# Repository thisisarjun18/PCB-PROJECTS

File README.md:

# PCB-PROJECTS
PCB design projects created in KiCad, including schematic capture, PCB layout, routing, and hardware prototyping.

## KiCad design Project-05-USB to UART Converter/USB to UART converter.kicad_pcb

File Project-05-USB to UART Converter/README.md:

Overview

This project is a USB Type-C to UART Converter designed using the CP2102N USB-to-UART Bridge Controller.
It enables communication between a computer and microcontrollers, development boards, or embedded systems through a standard UART interface.
The board uses a USB Type-C connector for power and data transfer and exposes UART signals through external header pins.

Features
USB Type-C Interface
CP2102N USB-to-UART Bridge
UART Communication (TX/RX)
Reset Signal Access
Compact and Easy-to-Use Design
Plug-and-Play USB Connectivity
Suitable for Embedded Development and Debugging
Components Used
CP2102N USB-to-UART Bridge IC
USB Type-C Connector
Status LEDs
Decoupling Capacitors
Pull-up/Pull-down Resistors
UART Header Connector
PCB Designed in KiCad
Pin Configuration
Pin	Description
VBUS	+5V USB Supply
GND	Ground
TX	UART Transmit
RX	UART Receive
RST	Reset Signal
Working Principle
The USB Type-C connector receives power and USB data from the host computer.
The CP2102N enumerates as a virtual COM port on the operating system.
USB data is converted into UART serial data.
The TX and RX pins provide serial communication with external microcontrollers or embedded devices.
Status LEDs indicate power and communication activity.
Applications
Microcontroller Programming
Serial Debugging
Embedded System Development
Firmware Uploading
IoT Prototyping
UART Communication Testing

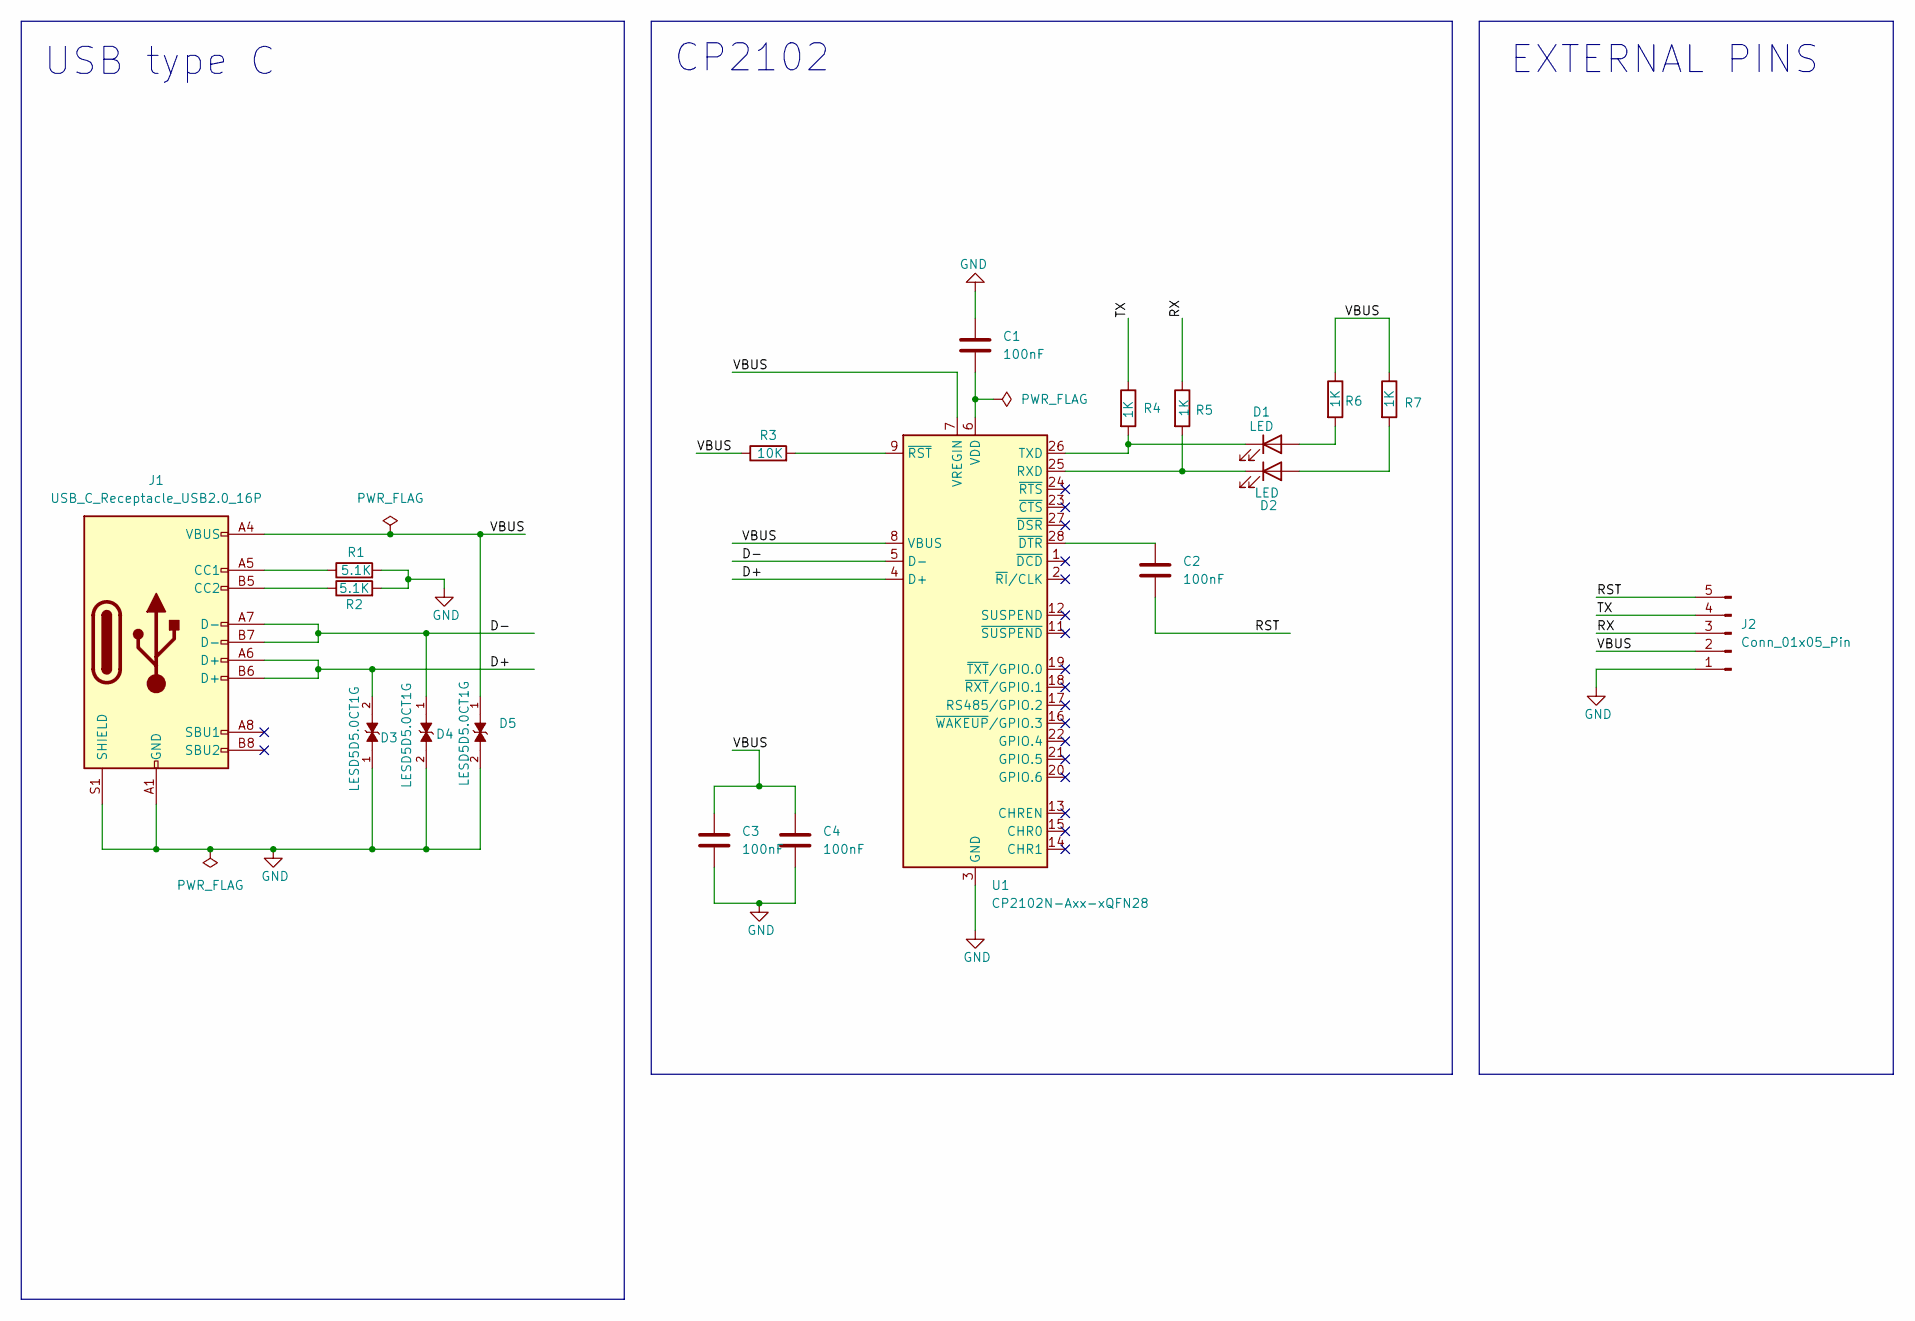
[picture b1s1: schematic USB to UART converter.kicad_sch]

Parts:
C1, C2, C3, C4: 100nF; C_0201_0603Metric
D1, D2: LED; LED_0201_0603Metric
D3, D4, D5: LESD5D5.0CT1G; TVS_LESD5D5.0CT1G; PARTREV O
J1: USB_C_Receptacle_USB2.0_16P; USB_C_Receptacle_HRO_TYPE-C-31-M-12
J2: Conn_01x05_Pin; PinHeader_1x05_P2.54mm_Horizontal
R1, R2: 5.1K; R_0201_0603Metric
R3: 10K; R_0201_0603Metric
R4, R5, R6, R7: 1K; R_0201_0603Metric
U1: CP2102N-Axx-xQFN28; QFN-28-1EP_5x5mm_P0.5mm_EP3.35x3.35mm

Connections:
/D+: D3.2, J1.A6 (D+), J1.B6 (D+), U1.4 (D+)
/D-: D4.1, J1.A7 (D-), J1.B7 (D-), U1.5 (D-)
/RST: C2.1, J2.5
/RX: J2.3, R5.1
/TX: J2.4, R4.1
/VBUS: C3.1, C4.1, D5.1, J1.A4 (VBUS), J1.A9 (VBUS), J1.B4 (VBUS), J1.B9 (VBUS), J2.2, R3.1, R6.1, R7.1, U1.7 (VREGIN), U1.8 (VBUS)
GND: C1.1, C3.2, C4.2, D3.1, D4.2, D5.2, J1.A1 (GND), J1.A12 (GND), J1.B1 (GND), J1.B12 (GND), J1.S1 (SHIELD), J2.1, R1.2, R2.2, U1.3 (GND), U1.29 (GND)
unnamed: D1.2 (A), R6.2
unnamed: D1.1 (K), R4.2, U1.26 (TXD)
unnamed: D2.2 (A), R7.2
unnamed: D2.1 (K), R5.2, U1.25 (RXD)
unnamed: J1.A5 (CC1), R1.1
unnamed: J1.B5 (CC2), R2.1
unnamed: C1.2, U1.6 (VDD)
unnamed: C2.2, U1.28 (~DTR)
unnamed: R3.2, U1.9 (~RST)

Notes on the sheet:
CP2102
USB type C
EXTERNAL PINS

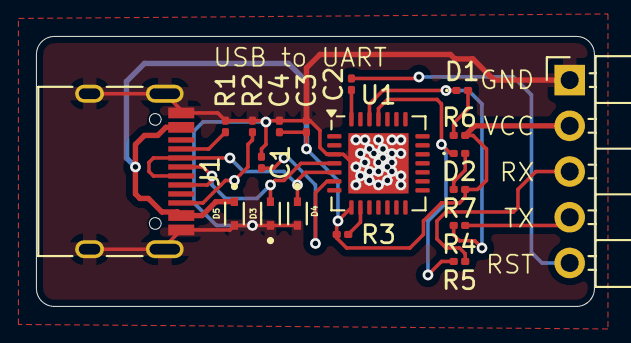
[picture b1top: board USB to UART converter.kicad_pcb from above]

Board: 2 copper layers, 31.0 x 15.0 mm, 19 parts (0 on the bottom side), 16 nets.

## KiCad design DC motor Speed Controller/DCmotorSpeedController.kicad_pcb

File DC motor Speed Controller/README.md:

Overview

This project implements a PWM-based DC Motor Speed Controller using the NE555 Timer IC and a TIP122 Darlington Transistor.
The speed of the motor is controlled by adjusting the duty cycle of the PWM signal through a potentiometer, 
allowing efficient motor speed regulation without significant power loss.

Circuit Description

The NE555 timer is configured in astable mode to generate a PWM signal.
A potentiometer and two diodes are used to independently control the charging and discharging paths of the timing capacitor,
enabling duty-cycle adjustment while maintaining a nearly constant frequency.

The generated PWM signal drives a TIP122 transistor, which acts as a switching element for the DC motor. 
A flyback diode protects the transistor from back-EMF generated by the motor.

Components Used
NE555 Timer IC
TIP122 Darlington Transistor
100kΩ Potentiometer
1kΩ Resistors (R1, R2)
2.2kΩ Resistor (R3)
1N4007 Diodes (D1, D2, D3)
LED Indicator
100nF Capacitors (C1, C2)
1000µF Capacitor (C3)
DC Motor
DC Power Supply
Features
PWM-based speed control
Smooth motor operation
Low component count
Back-EMF protection
Easy to build and understand
Suitable for learning PWM motor control concepts
Working Principle
The NE555 generates a PWM waveform.
The potentiometer adjusts the duty cycle.
The PWM output drives the TIP122 transistor.
The transistor switches power to the motor.
Higher duty cycle → Higher average voltage → Higher motor speed.
Lower duty cycle → Lower average voltage → Lower motor speed.
Applications
Robotics
DIY Electronics Projects
Fan Speed Controllers
Small Automation Systems
Educational Embedded Projects

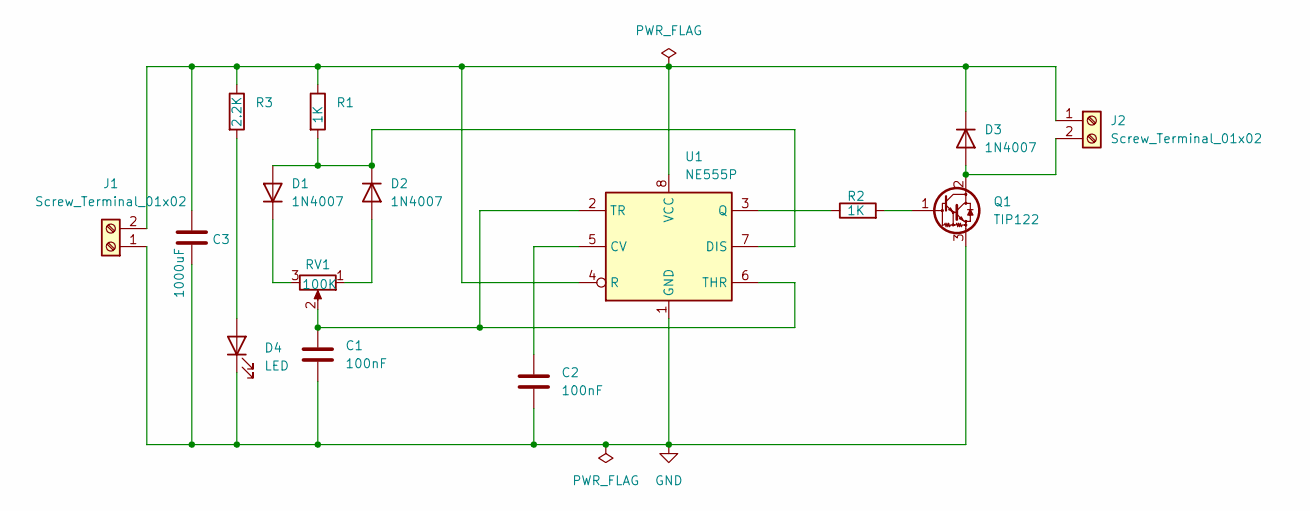
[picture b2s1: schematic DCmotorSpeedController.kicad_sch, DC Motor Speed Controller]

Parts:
C1, C2: 100nF; C_Disc_D4.7mm_W2.5mm_P5.00mm
C3: 1000uF; CP_Radial_D10.0mm_P5.00mm
D1, D2, D3: 1N4007; D_DO-41_SOD81_P10.16mm_Horizontal
D4: LED; LED_D5.0mm
J1, J2: Screw_Terminal_01x02; TerminalBlock_bornier-2_P5.08mm
Q1: TIP122; TO-220-3_Vertical
R1, R2: 1K; R_Axial_DIN0204_L3.6mm_D1.6mm_P7.62mm_Horizontal
R3: 2.2K; R_Axial_DIN0204_L3.6mm_D1.6mm_P7.62mm_Horizontal
RV1: 100K; Potentiometer_Alps_RK163_Single_Horizontal
U1: NE555P; DIP-8_W7.62mm

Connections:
GND: C1.2, C2.2, C3.2, D4.1 (K), J1.1, Q1.3 (E), U1.1 (GND)
unnamed: D1.2 (A), D2.1 (K), R1.2, U1.7 (DIS)
unnamed: D1.1 (K), RV1.3
unnamed: D2.2 (A), RV1.1
unnamed: D3.2 (A), J2.2, Q1.2 (C)
unnamed: C3.1, D3.1 (K), J1.2, J2.1, R1.1, R3.1, U1.4 (R), U1.8 (VCC)
unnamed: D4.2 (A), R3.2
unnamed: Q1.1 (B), R2.2
unnamed: C2.1, U1.5 (CV)
unnamed: R2.1, U1.3 (Q)
unnamed: C1.1, RV1.2, U1.2 (TR), U1.6 (THR)

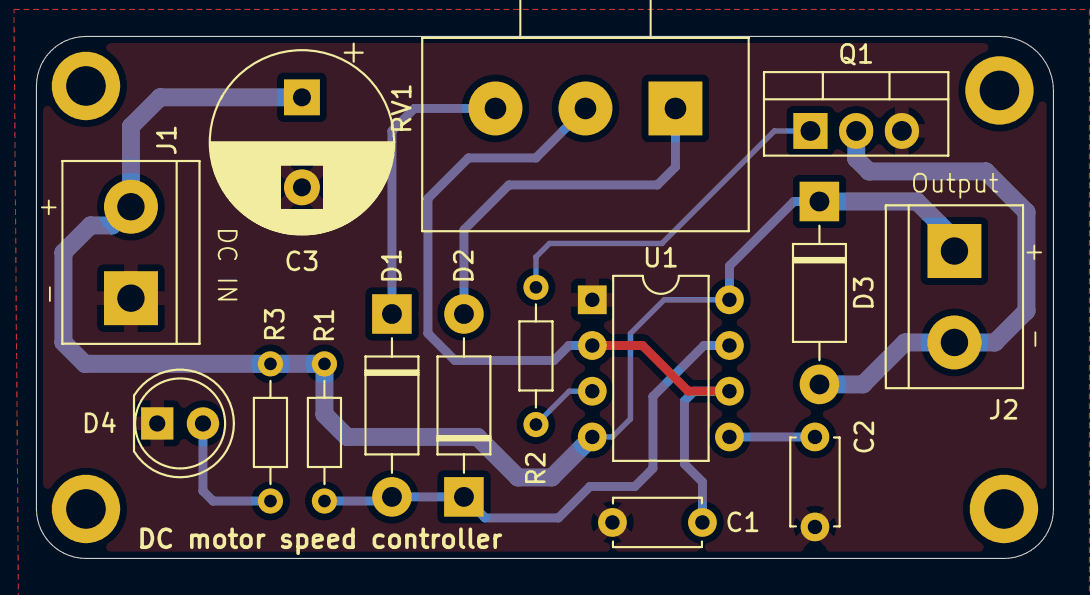
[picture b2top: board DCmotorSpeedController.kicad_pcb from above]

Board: 2 copper layers, 56.5 x 29.0 mm, 15 parts (0 on the bottom side), 11 nets.

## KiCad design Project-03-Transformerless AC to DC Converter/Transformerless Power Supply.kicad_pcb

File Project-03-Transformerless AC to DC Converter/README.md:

Transformerless AC to DC Converter PCB Design

Overview

This project is a PCB design of a Transformerless AC to DC Converter created using KiCad. The circuit converts AC input into regulated DC output using a capacitive dropper, bridge rectifier, filter capacitors, and a voltage regulator.

The design demonstrates fundamental concepts of power electronics, PCB layout design, component placement, routing, ground plane implementation, and Design Rule Checking (DRC).

Features

* AC to DC conversion without a transformer
* Bridge rectifier using four diodes
* Capacitive dropper technique
* Voltage regulation
* Ground plane implementation on the PCB
* Designed using KiCad 10
* DRC verified with no electrical errors

## Components Used

* Terminal Blocks
* Capacitive Dropper Capacitor
* Resistors
* Bridge Rectifier Diodes
* Electrolytic Capacitors
* Ceramic Capacitor
* Voltage Regulator
* LED Indicator

PCB Design Highlights

* Single PCB design with optimized component placement
* Ground plane implemented using copper pour
* Through-hole components for easy assembly
* Electrical Rule Check (ERC) and Design Rule Check (DRC) completed

Learning Outcomes

This project helped in understanding:

* AC to DC conversion principles
* Bridge rectifier operation
* Capacitor filtering
* Voltage regulation
* PCB routing techniques
* Ground plane implementation
* KiCad schematic and PCB workflow

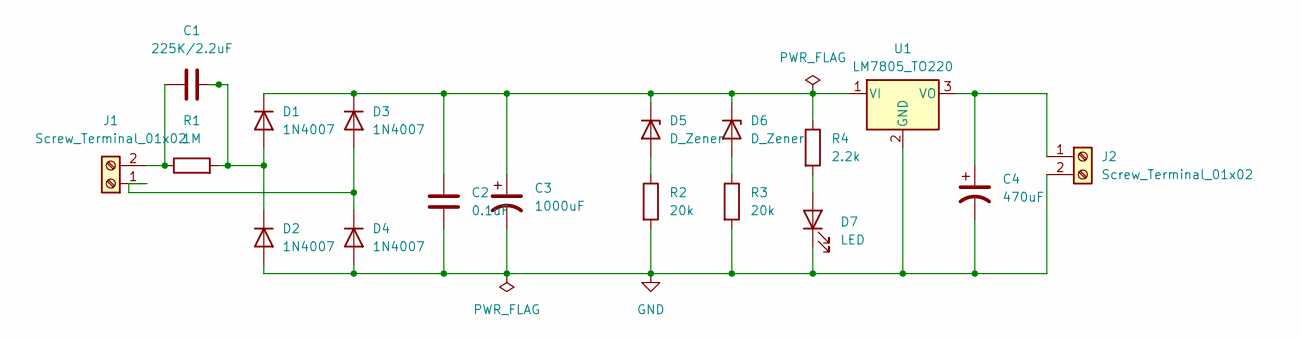
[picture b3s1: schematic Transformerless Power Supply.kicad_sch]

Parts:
C1: 225K/2.2uF; C_Rect_L10.0mm_W3.0mm_P7.50mm_FKS3_FKP3
C2: 0.1uF; C_Disc_D10.0mm_W2.5mm_P5.00mm
C3: 1000uF; CP_Radial_D10.0mm_P2.50mm
C4: 470uF; CP_Radial_D10.0mm_P3.80mm
D1, D2, D3, D4: 1N4007; D_DO-41_SOD81_P10.16mm_Horizontal
D5, D6: D_Zener; D_DO-15_P12.70mm_Horizontal
D7: LED; LED_D3.0mm
J1, J2: Screw_Terminal_01x02; TerminalBlock_MaiXu_MX126-5.0-02P_1x02_P5.00mm
R1: 1M; R_Axial_DIN0204_L3.6mm_D1.6mm_P5.08mm_Horizontal
R2, R3: 20k; R_Axial_DIN0204_L3.6mm_D1.6mm_P5.08mm_Horizontal
R4: 2.2k; R_Axial_DIN0204_L3.6mm_D1.6mm_P5.08mm_Horizontal
U1: LM7805_TO220; TO-220-3_Vertical

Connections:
GND: C2.2, C3.2, C4.2, D2.2 (A), D4.2 (A), D7.1 (K), J2.2, R2.2, R3.2, U1.2 (GND)
unnamed: C1.2, D1.2 (A), D2.1 (K), R1.2
unnamed: C2.1, C3.1, D1.1 (K), D3.1 (K), D5.1 (K), D6.1 (K), R4.1, U1.1 (VI)
unnamed: D3.2 (A), D4.1 (K), J1.1
unnamed: D5.2 (A), R2.1
unnamed: D6.2 (A), R3.1
unnamed: D7.2 (A), R4.2
unnamed: C1.1, J1.2, R1.1
unnamed: C4.1, J2.1, U1.3 (VO)

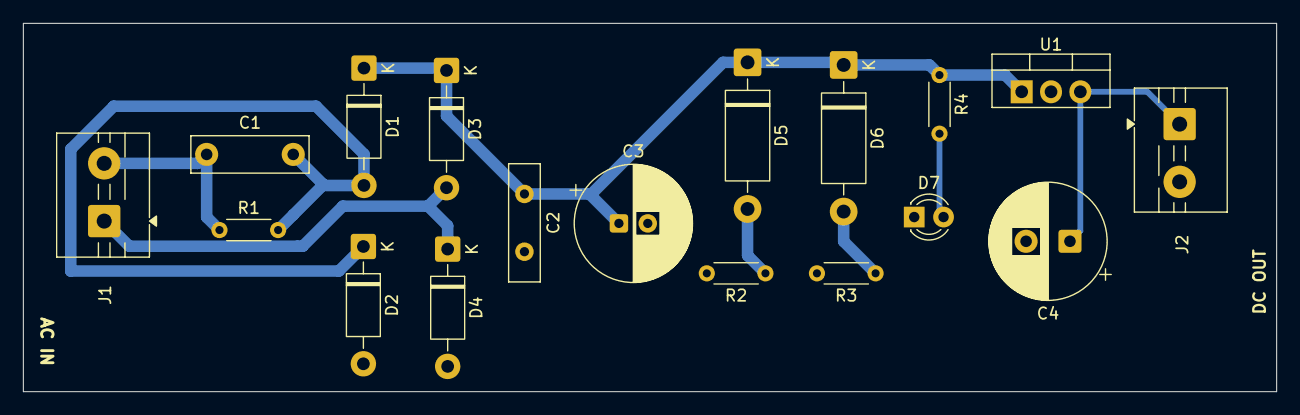
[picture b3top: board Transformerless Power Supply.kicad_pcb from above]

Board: 2 copper layers, 108.6 x 31.9 mm, 18 parts (0 on the bottom side), 9 nets.

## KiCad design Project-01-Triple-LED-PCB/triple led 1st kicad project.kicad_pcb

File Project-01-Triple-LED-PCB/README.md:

# Project 01 - Triple LED PCB

A simple 3-channel LED indicator PCB designed in KiCad.

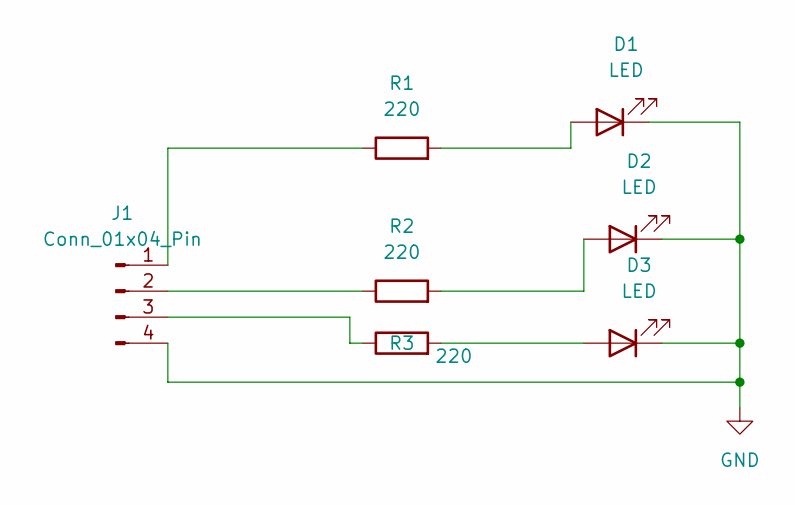
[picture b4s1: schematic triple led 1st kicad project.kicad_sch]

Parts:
D1, D2, D3: LED; LED_D5.0mm
J1: Conn_01x04_Pin; PinHeader_1x04_P1.00mm_Vertical
R1, R2, R3: 220; R_Axial_DIN0204_L3.6mm_D1.6mm_P5.08mm_Horizontal

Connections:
GND: D1.1 (K), D2.1 (K), D3.1 (K), J1.4
unnamed: D1.2 (A), R1.2
unnamed: D2.2 (A), R2.2
unnamed: D3.2 (A), R3.2
unnamed: J1.1, R1.1
unnamed: J1.2, R2.1
unnamed: J1.3, R3.1

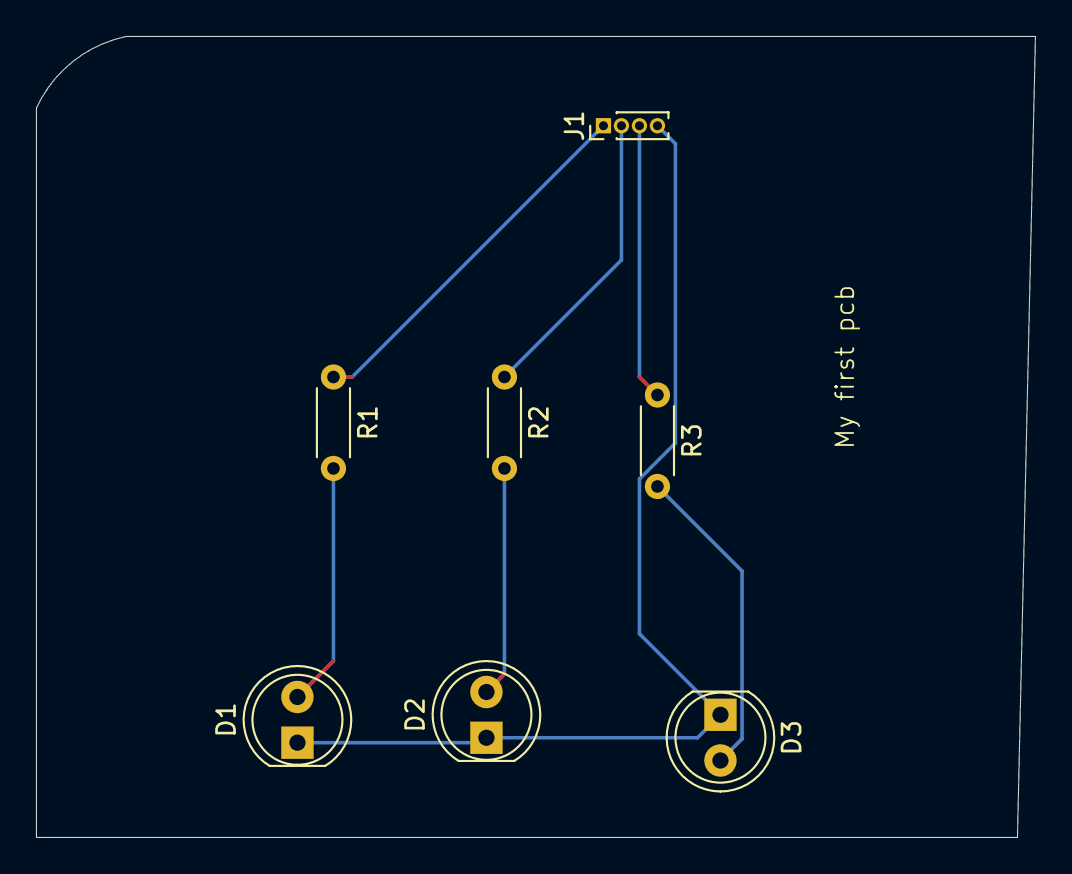
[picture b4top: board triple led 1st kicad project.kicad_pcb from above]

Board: 2 copper layers, 55.5 x 44.5 mm, 7 parts (0 on the bottom side), 7 nets.

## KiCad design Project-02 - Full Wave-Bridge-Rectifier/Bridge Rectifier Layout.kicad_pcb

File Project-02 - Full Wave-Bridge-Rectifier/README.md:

# Project 02 - Full Wave Bridge Rectifier

## Overview
A full-wave bridge rectifier PCB designed in KiCad to convert AC voltage into DC voltage using four 1N4007 diodes, a filter capacitor, and an LED power indicator.

## Components Used
- 4 × 1N4007 Diodes
- 1 × 1000µF Capacitor
- 1 × LED
- 1 × 2.2kΩ Resistor
- 2 × Screw Terminal Connectors

## Features
- Full-wave AC to DC conversion
- Capacitor filtering for smoother DC output
- LED power indication
- Through-hole components

## Tools Used
- KiCad 10

## Learning Outcomes
- Bridge rectifier operation
- AC to DC conversion
- Capacitor filtering
- Schematic design
- PCB layout and routing

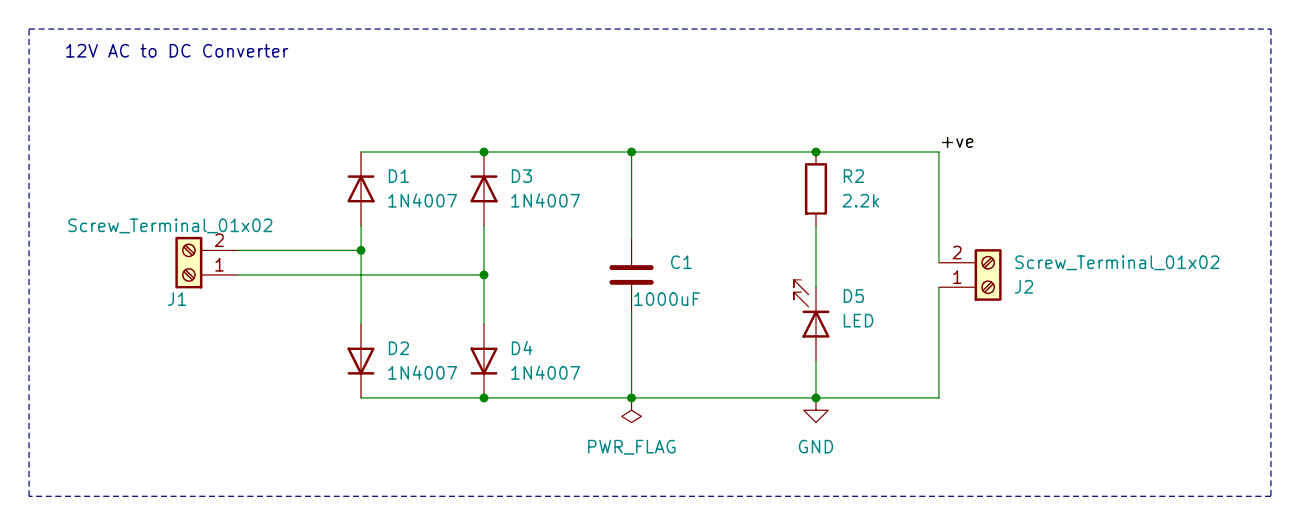
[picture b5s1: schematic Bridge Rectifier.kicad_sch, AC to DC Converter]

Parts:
C1: 1000uF; CP_Radial_D10.0mm_P3.50mm
D1, D2, D3, D4: 1N4007; D_DO-41_SOD81_P10.16mm_Horizontal
D5: LED; LED_D10.0mm
J1, J2: Screw_Terminal_01x02
R2: 2.2k; R_Axial_DIN0207_L6.3mm_D2.5mm_P10.16mm_Horizontal

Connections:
/+ve: C1.1, D1.1 (K), D3.1 (K), J2.2, R2.1
GND: C1.2, D2.1 (K), D4.1 (K), D5.2 (A), J2.1
unnamed: D1.2 (A), D2.2 (A), J1.2
unnamed: D3.2 (A), D4.2 (A), J1.1
unnamed: D5.1 (K), R2.2

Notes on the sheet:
12V AC to DC Converter

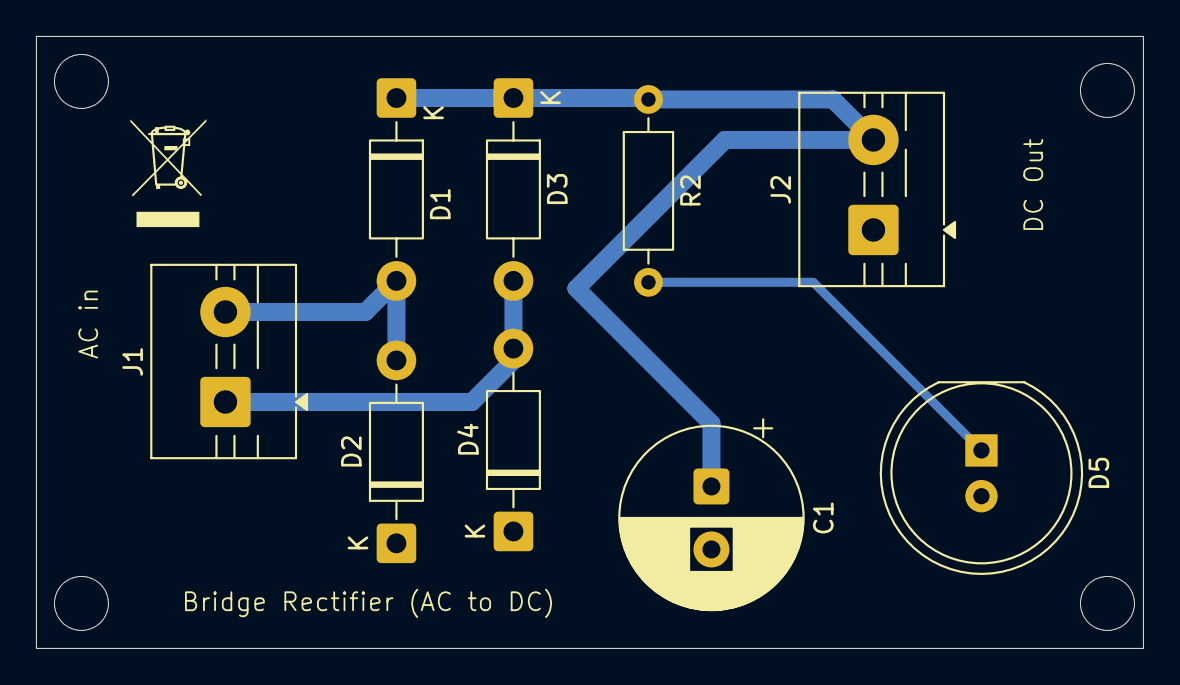
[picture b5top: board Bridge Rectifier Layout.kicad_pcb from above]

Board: 2 copper layers, 61.5 x 34.0 mm, 9 parts (0 on the bottom side), 5 nets.

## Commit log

2026-06-09 Create Project-01 Triple LED PCB folder
2026-06-09 Add KiCad files, PCB layout, schematic, and 3D model images
    A simple 3-channel LED indicator PCB designed using KiCad. The project consists of three LEDs, three 220Ω current-limiting resistors, and a 4-pin connector. It was created to learn schematic design, 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
2026-06-09 Create Project-02 Full Wave Bridge Rectifier
2026-06-09 Add project files, PCB schematic, PCB layout, 3D model images, and original KiCad files
2026-06-10 PCB designs for transformerless AC to DC converter
2026-06-10 Adding PCB Designs | Schematic | Layout | 3D Model Pictures
2026-06-10 Initial PCB design for transformerless AC to DC converter
2026-06-10 Adding PCB Designs | Schematics | Layout | 3D Pictures of PCB
2026-06-10 adding step file for screw terminal
2026-06-10 Add kicad pro file
2026-06-10 Adding PCB Designs
2026-06-10 Adding PCB Designs | Schematic | Layout | 3D Graphic Pictures
2026-06-10 adding pro file
2026-06-10 Create README.md for pictures directory
    Add a README file for the pictures directory.
2026-06-10 Adding Pictures
2026-06-22 Add README for DC Motor Speed Controller project
    This README provides an overview of the PWM-based DC Motor Speed Controller project, including circuit description, components used, features, working principle, and applications.
2026-06-22 uploading files of DC Motor Speed Controller
2026-06-22 Add README for USB to UART Converter project
    This README provides an overview of the USB Type-C to UART Converter project, including features, components, pin configuration, working principle, and applications.
2026-06-22 Add USB to UART Files
